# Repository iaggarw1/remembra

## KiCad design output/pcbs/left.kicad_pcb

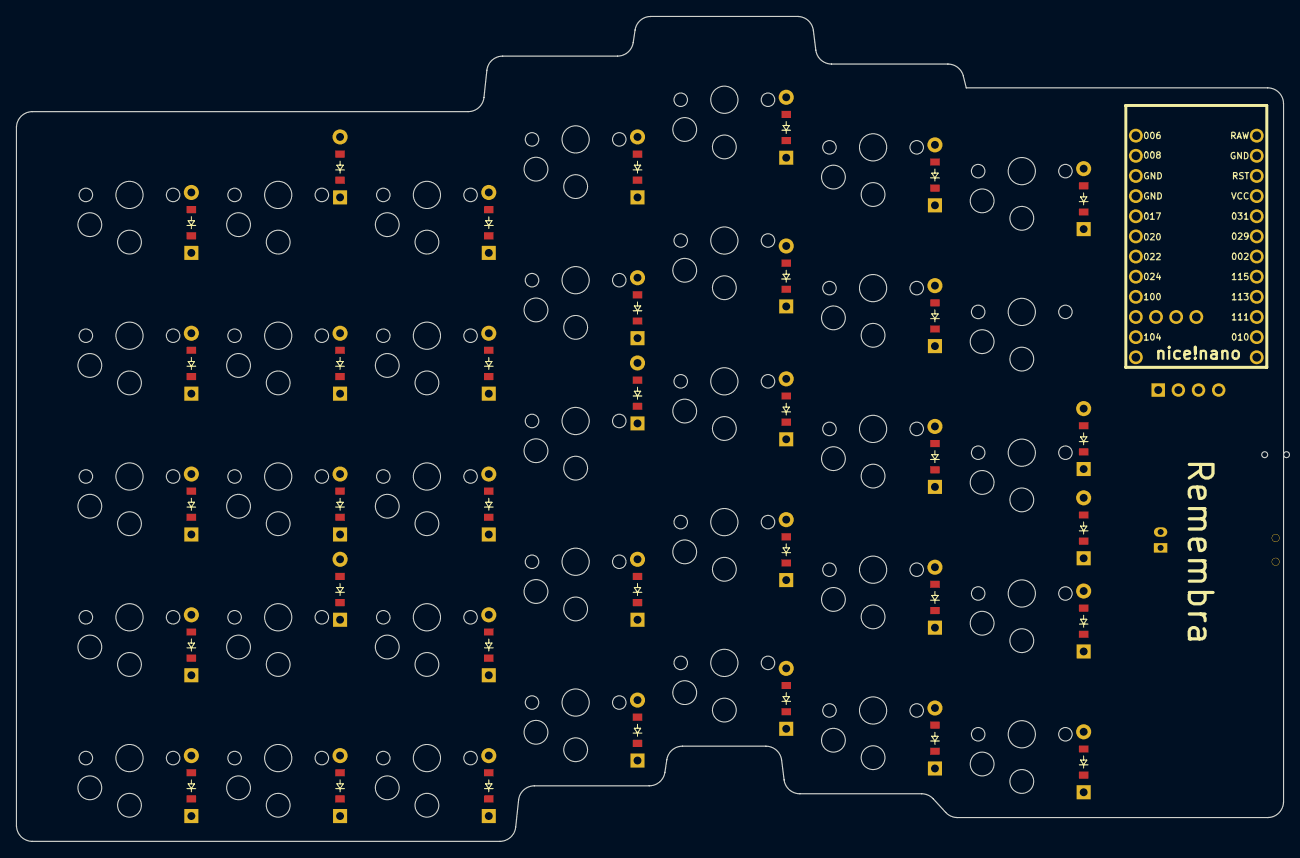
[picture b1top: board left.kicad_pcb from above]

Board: 2 copper layers, 159.8 x 104.0 mm, 75 parts (0 on the bottom side), 52 nets, no tracks yet.

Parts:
B1: Panasonic_EVQPUL_EVQPUC
D1, D2, D3, D4, D5, D6, D7, D8, D9, D10, D11, D12, D13, D14, D15, D16, D17, D18, D19, D20, D21, D22, D23, D24, D25, D26, D27, D28, D29, D30, D31, D32, D33, D34, D35: ComboDiode
JST1: JST_PH_S2B-PH-K_02x2.00mm_Angled
MCU1: nice_nano
OLED1: OLED; OLED_headers
S1, S2, S3, S4, S5, S6, S7, S8, S9, S10, S11, S12, S13, S14, S15, S16, S17, S18, S19, S20, S21, S22, S23, S24, S25, S26, S27, S28, S29, S30, S31, S32, S33, S34, S35: PG1350
T1: SPDT_C128955

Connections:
GND: B1.1, JST1.2, MCU1.3, MCU1.4, MCU1.23, OLED1.1
P002: D3.1, D7.1, D11.1, D19.1, D23.1, D30.1, D33.1, MCU1.18
P011: MCU1.10, S26.1, S27.1, S28.1, S29.1, S30.1
P017: MCU1.5, S31.1, S32.1, S33.1, S34.1, S35.1
P020: MCU1.6, S6.1, S7.1, S8.1, S9.1, S10.1
P022: MCU1.7, S11.1, S12.1, S13.1, S14.1, S15.1
P024: MCU1.8, S16.1, S17.1, S18.1, S19.1, S20.1
P029: D4.1, D8.1, D12.1, D16.1, D24.1, D29.1, D35.1, MCU1.19
P031: D5.1, D13.1, D17.1, D20.1, D25.1, D28.1, D32.1, MCU1.20
P100: MCU1.9, S21.1, S22.1, S23.1, S24.1, S25.1
P111: MCU1.15, S1.1, S2.1, S3.1, S4.1, S5.1
P113: D1.1, D6.1, D9.1, D14.1, D21.1, D26.1, D34.1, MCU1.16
P115: D2.1, D10.1, D15.1, D18.1, D22.1, D27.1, D31.1, MCU1.17
RAW: MCU1.24, T1.2
RST: B1.2, MCU1.22
VCC: MCU1.21, OLED1.2
fifth_bottom: D22.2, S27.2
fifth_home: D23.2, S28.2
fifth_mod: D21.2, S26.2
fifth_num: D25.2, S30.2
fifth_top: D24.2, S29.2
first_bottom: D31.2, S7.2
first_home: D7.2, S8.2
first_mod: D6.2, S6.2
first_num: D32.2, S10.2
first_top: D8.2, S9.2
fourth_bottom: D18.2, S22.2
fourth_home: D19.2, S23.2
fourth_mod: D34.2, S21.2
fourth_num: D20.2, S25.2
fourth_top: D35.2, S24.2
pos: JST1.1, T1.1
second_bottom: D10.2, S12.2
second_home: D11.2, S13.2
second_mod: D9.2, S11.2
second_num: D13.2, S15.2
second_top: D12.2, S14.2
seventh_bottom: D2.2, S2.2
seventh_home: D3.2, S3.2
seventh_mod: D1.2, S1.2
seventh_num: D5.2, S5.2
seventh_top: D4.2, S4.2
sixth_bottom: D27.2, S32.2
sixth_home: D30.2, S33.2
sixth_mod: D26.2, S31.2
sixth_num: D28.2, S35.2
sixth_top: D29.2, S34.2
third_bottom: D15.2, S17.2
third_home: D33.2, S18.2
third_mod: D14.2, S16.2
third_num: D17.2, S20.2
third_top: D16.2, S19.2

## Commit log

2025-04-16 feat: config, pcb, footprint added to repo
2025-04-16 fix: removed project files. git ignore tbd
2025-04-16 chore: remove extra config file
2025-04-19 adding tenting puck
